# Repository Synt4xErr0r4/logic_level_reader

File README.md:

# logic level reader

A simple 8-pin 5V logic level reader with USB interface and.

Uses an ATmega48PB microcontroller for processing and an MCP2221A for making the ATmega's UART interface available over USB-C.

The ATmega is programmed using a USBasp using the 6-pin header and the Ardunio IDE (`logic_level_reader.ino`).

The device will periodically (every ~100ms) print the state of all pins (each line formatted as `<pin> <state>`,
where `pin` is the pin number (0 through 8), and `state` is `0=low`, `1=high`, or `2=floating`).
I haven't made a program yet that actually parses that data.

Pin 0 is connected to a pogo pin as well as the red-green LED.
For LOW, the red LED will light up, for HIGH, the green LED will light up, and for FLOATING, both will light up (resulting in an orange color).

The level sensing is done by first pulling the pin LOW (through 47k), then pulling it HIGH (also through 47k).
If the levels disagree, the pin is considered floating.

The pin closest to the USB port is GND and must be connected to the DUT's GND.

Note that this method of measuring can affect the DUT by pulling lines low/high!
Also, this doesn't work for high-frequency signals.
So, if you want to do some actual logic level analysis, you'd be better off using a proper logic level analyzer!

And the board probably wildly exceeds the allowed USB VBUS capacitance!

The PCB was designed in KiCAD and manufactured by JLCPCB.
Also, it's a 6-layer PCB because JLC had an offer back when I made this, so the PCB with ENIG and epoxy filled & capped vias only cost me <2€ (without shipping).
So, if you were to order this today, it'll probably cost somewhere in the neighborhood of 40€.

I also made a 3D printed case (PETG).

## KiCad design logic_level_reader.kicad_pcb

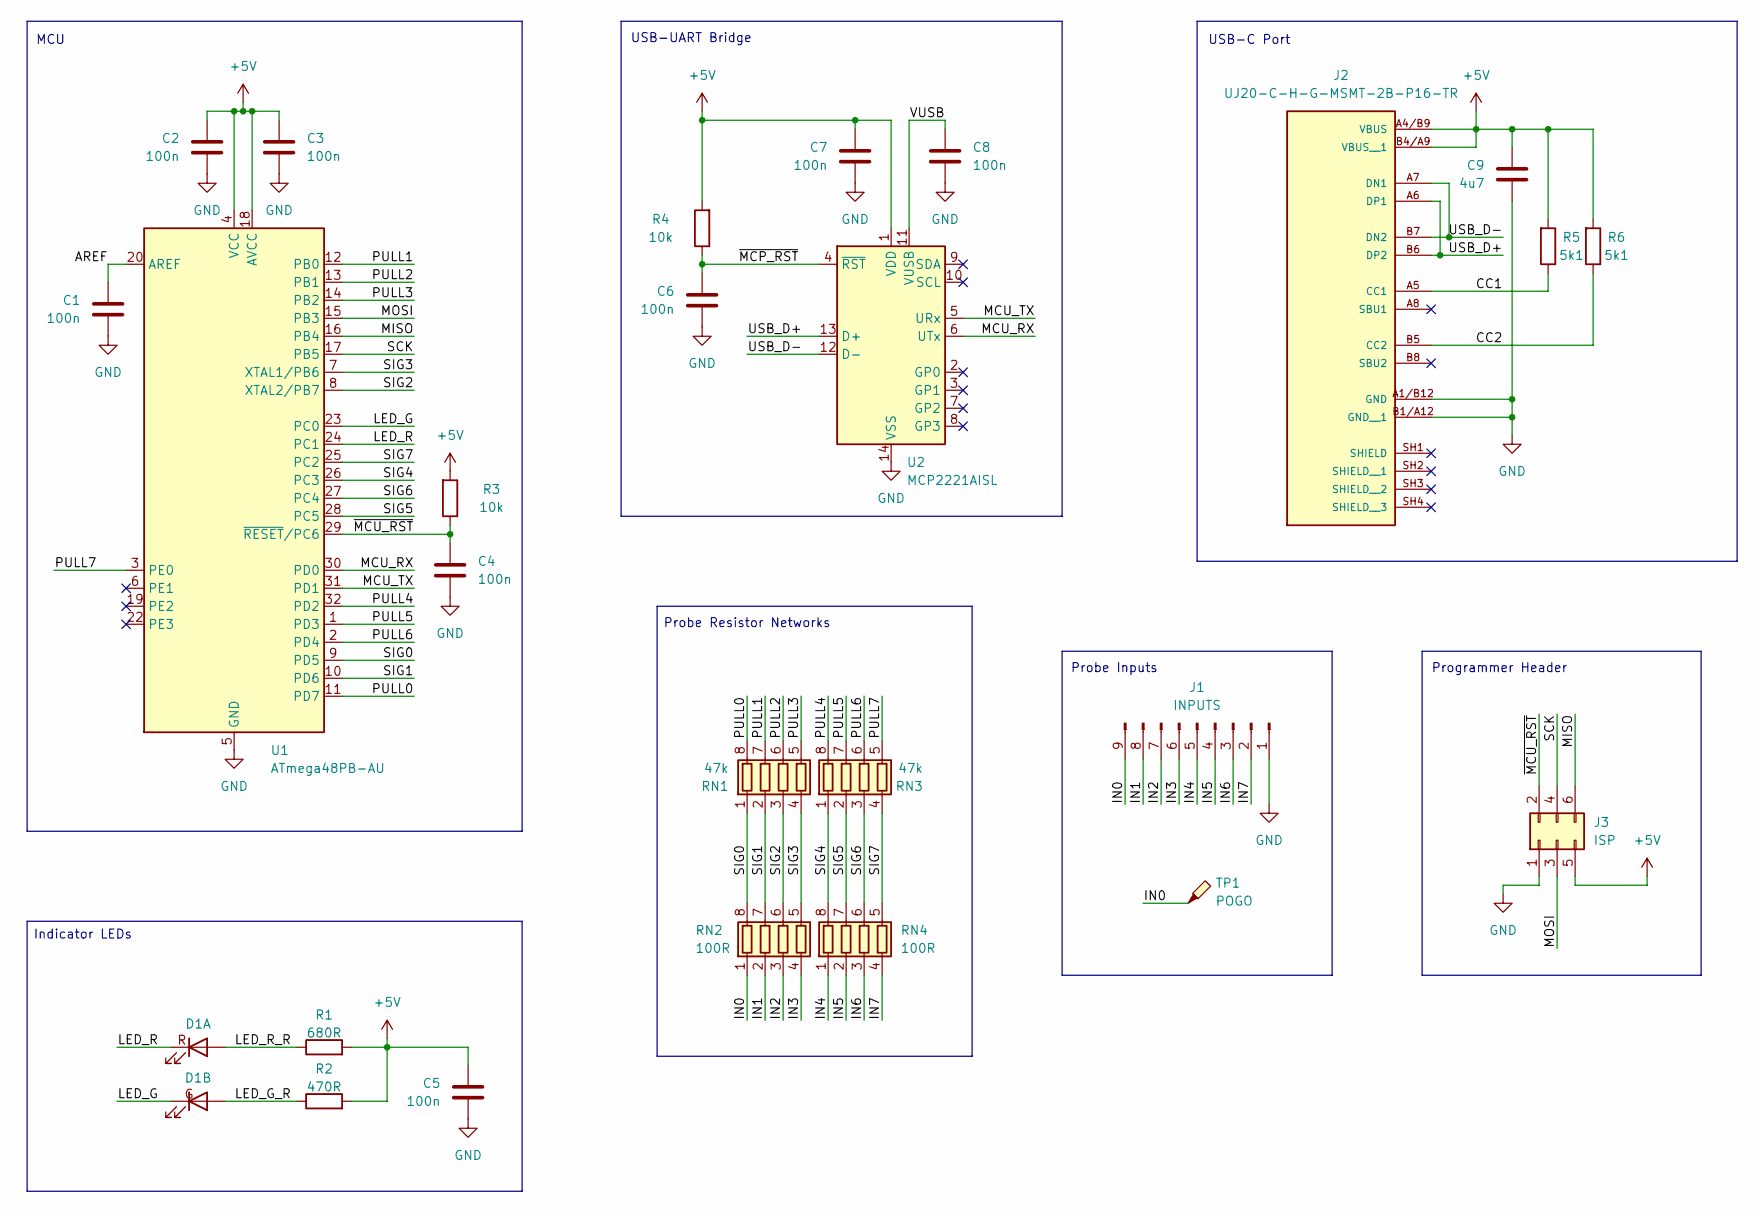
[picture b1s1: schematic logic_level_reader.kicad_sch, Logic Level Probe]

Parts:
C1, C2, C3, C4, C5, C6, C7, C8: 100n; C_1206_3216Metric
C9: 4u7; C_1206_3216Metric
D1: LC295JRJGCT-U1
J1: INPUTS; PinHeader_1x09_P2.54mm_Vertical
J2: UJ20-C-H-G-MSMT-2B-P16-TR; SAMESKY_UJ20-C-H-G-MSMT-2B-P16-TR; PARTREV 1.0
J3: ISP; PinHeader_2x03_P2.54mm_Vertical
R1: 680R; R_1206_3216Metric
R2: 470R; R_1206_3216Metric
R3, R4: 10k; R_1206_3216Metric
R5, R6: 5k1; R_1206_3216Metric
RN1, RN3: 47k; YC164-JR-07xL
RN2, RN4: 100R; YC164-JR-07xL
TP1: POGO; SolderWirePad_1x01_SMD_2x4mm
U1: ATmega48PB-AU; TQFP-32_7x7mm_P0.8mm
U2: MCP2221AISL; SOIC-14_3.9x8.7mm_P1.27mm

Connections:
+5V: C2.1, C3.1, C5.1, C7.1, C9.1, J2.A4/B9 (VBUS), J2.B4/A9 (VBUS__1), J3.5, R1.2, R2.2, R3.2, R4.2, R5.2, R6.2, U1.4 (VCC), U1.18 (AVCC), U2.1 (VDD)
/AREF: C1.1, U1.20 (AREF)
/CC1: J2.A5 (CC1), R5.1
/CC2: J2.B5 (CC2), R6.1
/IN0: J1.9, RN2.1 (R1.1), TP1.1 (1_1)
/IN1: J1.8, RN2.2 (R2.1)
/IN2: J1.7, RN2.3 (R3.1)
/IN3: J1.6, RN2.4 (R4.1)
/IN4: J1.5, RN4.1 (R1.1)
/IN5: J1.4, RN4.2 (R2.1)
/IN6: J1.3, RN4.3 (R3.1)
/IN7: J1.2, RN4.4 (R4.1)
/LED_G: D1.2 (K), U1.23 (PC0)
/LED_G_R: D1.4 (A), R2.1
/LED_R: D1.1 (K), U1.24 (PC1)
/LED_R_R: D1.3 (A), R1.1
/MCU_RX: U1.30 (PD0), U2.6 (UTx)
/MCU_TX: U1.31 (PD1), U2.5 (URx)
/MISO: J3.6, U1.16 (PB4)
/MOSI: J3.3, U1.15 (PB3)
/PULL0: RN1.8 (R1.2), U1.11 (PD7)
/PULL1: RN1.7 (R2.2), U1.12 (PB0)
/PULL2: RN1.6 (R3.2), U1.13 (PB1)
/PULL3: RN1.5 (R4.2), U1.14 (PB2)
/PULL4: RN3.8 (R1.2), U1.32 (PD2)
/PULL5: RN3.7 (R2.2), U1.1 (PD3)
/PULL6: RN3.6 (R3.2), U1.2 (PD4)
/PULL7: RN3.5 (R4.2), U1.3 (PE0)
/SCK: J3.4, U1.17 (PB5)
/SIG0: RN1.1 (R1.1), RN2.8 (R1.2), U1.9 (PD5)
/SIG1: RN1.2 (R2.1), RN2.7 (R2.2), U1.10 (PD6)
/SIG2: RN1.3 (R3.1), RN2.6 (R3.2), U1.8 (XTAL2/PB7)
/SIG3: RN1.4 (R4.1), RN2.5 (R4.2), U1.7 (XTAL1/PB6)
/SIG4: RN3.1 (R1.1), RN4.8 (R1.2), U1.26 (PC3)
/SIG5: RN3.2 (R2.1), RN4.7 (R2.2), U1.28 (PC5)
/SIG6: RN3.3 (R3.1), RN4.6 (R3.2), U1.27 (PC4)
/SIG7: RN3.4 (R4.1), RN4.5 (R4.2), U1.25 (PC2)
/USB_D+: J2.A6 (DP1), J2.B6 (DP2), U2.13 (D+)
/USB_D-: J2.A7 (DN1), J2.B7 (DN2), U2.12 (D-)
/VUSB: C8.1, U2.11 (VUSB)
/~MCP_RST: C6.1, R4.1, U2.4 (~RST)
/~MCU_RST: C4.1, J3.2, R3.1, U1.29 (~RESET/PC6)
GND: C1.2, C2.2, C3.2, C4.2, C5.2, C6.2, C7.2, C8.2, C9.2, J1.1, J2.A1/B12 (GND), J2.B1/A12 (GND__1), J3.1, U1.5 (GND), U1.21 (GND), U2.14 (VSS)

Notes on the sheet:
Programmer Header
USB-UART Bridge
USB-C Port
MCU
Probe Resistor Networks
Indicator LEDs
Probe Inputs

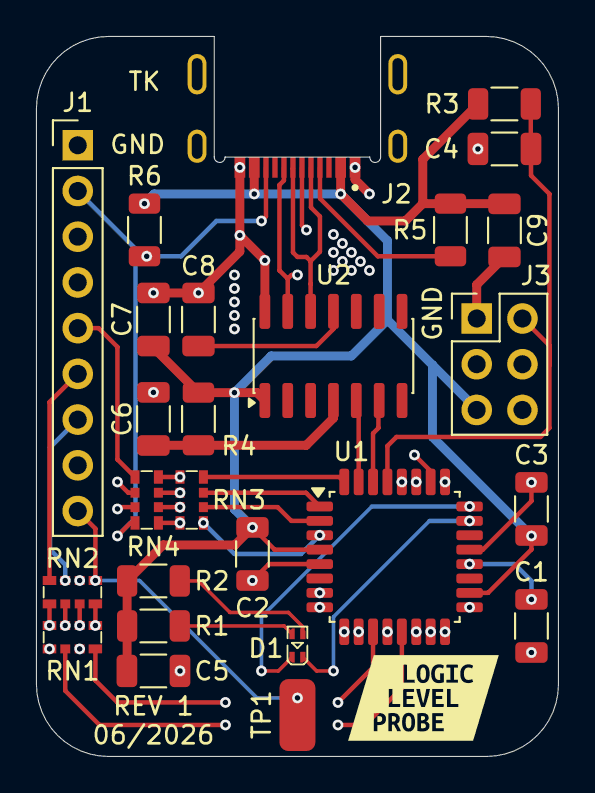
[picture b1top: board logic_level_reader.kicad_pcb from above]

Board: 6 copper layers, 29.0 x 40.0 mm, 27 parts (0 on the bottom side), 43 nets.

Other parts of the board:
kibuzzard-6A425033: G***; kibuzzard-6A425033

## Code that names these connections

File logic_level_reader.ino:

#define NCFG 8

struct PinConfig {
  uint8_t pull, sig;
};

enum PinLevel {
  LEVEL_LOW,
  LEVEL_HIGH,
  LEVEL_FLOATING
};

const PinConfig pincfg[NCFG] = {
  { PIN_PD7, PIN_PD5 },
  { PIN_PB0, PIN_PD6 },
  { PIN_PB1, PIN_PB7 },
  { PIN_PB2, PIN_PB6 },
  { PIN_PD2, PIN_PC3 },
  { PIN_PD3, PIN_PC5 },
  { PIN_PD4, PIN_PC4 },
  { PIN_PE0, PIN_PC2 },
};

void setup() {
  Serial.begin(115200);

  pinMode(PIN_PC0, OUTPUT);
  pinMode(PIN_PC1, OUTPUT);

  for (int i = 0; i < NCFG; ++i) {
    pinMode(pincfg[i].sig, INPUT);
    pinMode(pincfg[i].pull, OUTPUT);
    digitalWrite(pincfg[i].pull, LOW);
  }
}

void measure(int level, bool states[NCFG]) {
  for (int i = 0; i < NCFG; ++i) {
    digitalWrite(pincfg[i].pull, level);
  }
  
  delay(1);

  for (int i = 0; i < NCFG; ++i) {
    states[i] = digitalRead(pincfg[i].sig) != LOW;
  }
}

void loop() {
  bool states_lo[NCFG];
  bool states_hi[NCFG];
  PinLevel pinlevel[NCFG];

  measure(LOW, states_lo);
  measure(HIGH, states_hi);

  for (int i = 0; i < NCFG; ++i) {
    if (states_lo[i] != states_hi[i]) {
      pinlevel[i] = LEVEL_FLOATING;
    }
    else if (states_lo[i]) {
      pinlevel[i] = LEVEL_HIGH;
    }
    else {
      pinlevel[i] = LEVEL_LOW;
    }

    Serial.printf("%d %d\n", i, pinlevel[i]);
  }

  switch (pinlevel[0]) {
    case LEVEL_LOW:
      digitalWrite(PIN_PC0, HIGH);
      digitalWrite(PIN_PC1, LOW);
      break;
    
    case LEVEL_HIGH:
      digitalWrite(PIN_PC0, LOW);
      digitalWrite(PIN_PC1, HIGH);
      break;
    
    case LEVEL_FLOATING:
      digitalWrite(PIN_PC0, LOW);
      digitalWrite(PIN_PC1, LOW);
      break;
  }

  delay(100);
}
